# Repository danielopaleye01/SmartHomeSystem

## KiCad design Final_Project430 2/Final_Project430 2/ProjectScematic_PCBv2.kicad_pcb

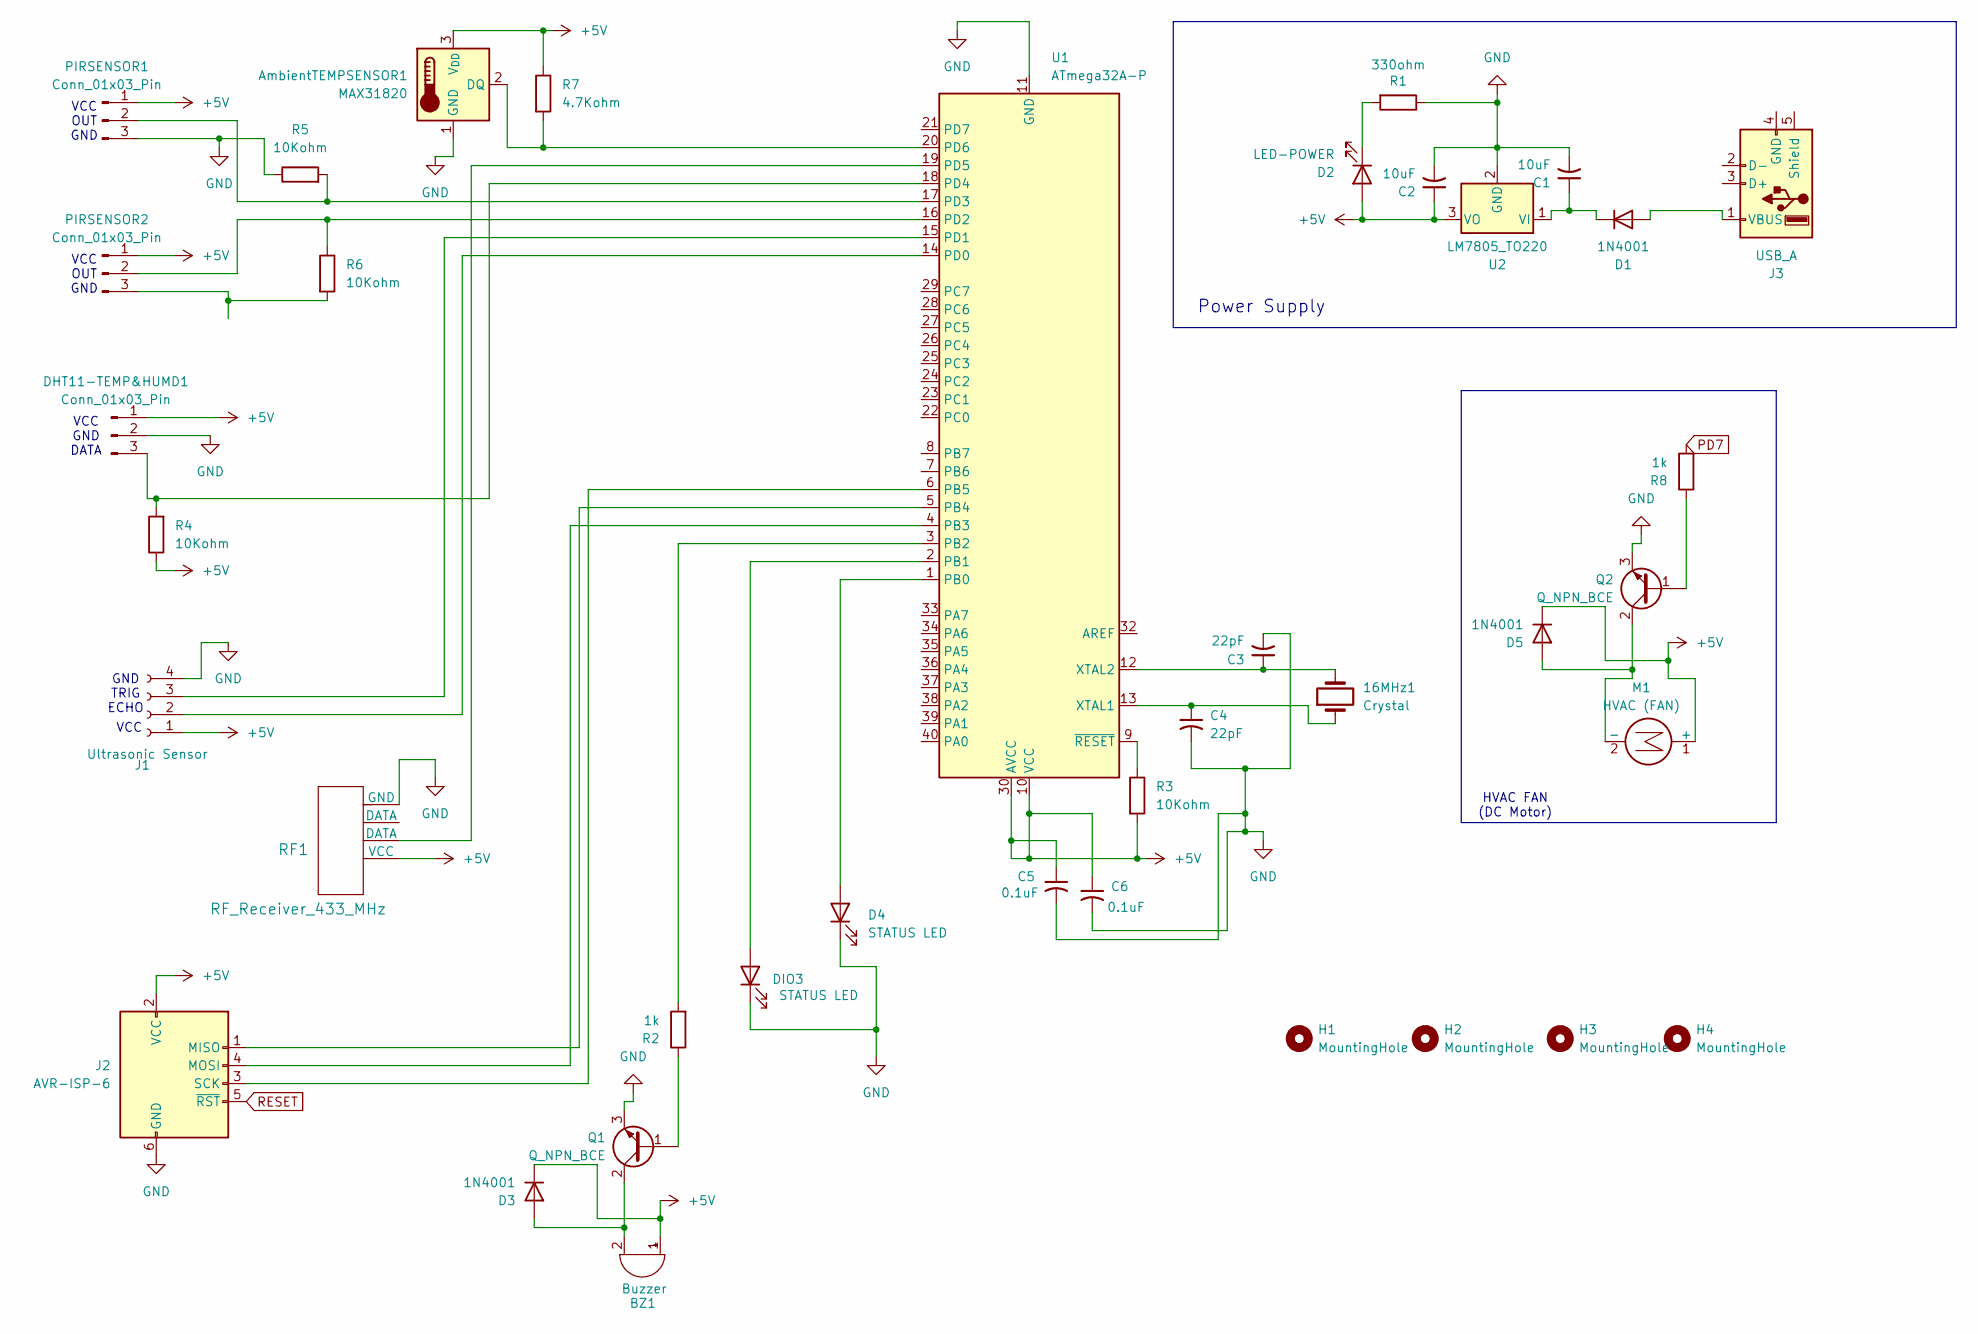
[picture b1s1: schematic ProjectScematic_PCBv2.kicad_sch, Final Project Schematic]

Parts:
16MHz1: Crystal; Crystal_HC49-U_Vertical
AmbientTEMPSENSOR1: MAX31820; TO-92_Inline
BZ1: Buzzer; Buzzer_12x9.5RM7.6
C1, C2: 10uF; C_Elec_5x5.4
C3, C4: 22pF; C_Elec_5x5.4
C5, C6: 0.1uF; C_Elec_5x5.4
D1, D3, D5: 1N4001; D_DO-41_SOD81_P10.16mm_Horizontal
D2: LED-POWER; LED_PLCC-2_3x2mm_AK
D4: STATUS LED; LED_1W_3W_R8
DHT11-TEMP&HUMD1: Conn_01x03_Pin; PinSocket_1x03_P2.54mm_Vertical
DIO3: STATUS LED; LED-L1T2_LUMILEDS
H1, H2, H3, H4: MountingHole; MountingHole_2.1mm
J1: Ultrasonic Sensor; AMS_OLGA12
J2: AVR-ISP-6; PinHeader_2x03_P2.54mm_Vertical
J3: USB_A; USB_A_CNCTech_1001-011-01101_Horizontal
M1: HVAC (FAN); FanPinHeader_1x03_P2.54mm_Vertical
PIRSENSOR1, PIRSENSOR2: Conn_01x03_Pin; FanPinHeader_1x03_P2.54mm_Vertical
Q1, Q2: Q_NPN_BCE; GaN_Systems_GaNPX-3_5x6.6mm_Drain2.93x0.6mm
R1: 330ohm; R_0201_0603Metric_Pad0.64x0.40mm_HandSolder
R2, R8: 1k; R_0201_0603Metric_Pad0.64x0.40mm_HandSolder
R3, R4, R5, R6: 10Kohm; R_0201_0603Metric_Pad0.64x0.40mm_HandSolder
R7: 4.7Kohm; R_0201_0603Metric_Pad0.64x0.40mm_HandSolder
RF1: RF_Receiver_433_MHz; Skyworks_SKY65404-31
U1: ATmega32A-P; DIP-40_W15.24mm
U2: LM7805_TO220; TO-220-3_Vertical

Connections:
+5V: AmbientTEMPSENSOR1.3 (V_{DD}), BZ1.1 (+), C2.1, C5.1, C6.1, D2.2 (A), D3.1 (K), D5.1 (K), DHT11-TEMP&HUMD1.1, J1.1, J2.2 (VCC), M1.1 (+), PIRSENSOR1.1, PIRSENSOR2.1, R3.2, R4.1, R7.1, RF1.1 (VCC), U1.10 (VCC), U1.30 (AVCC), U2.3 (VO)
GND: AmbientTEMPSENSOR1.1 (GND), C1.2, C2.2, C3.2, C4.2, C5.2, C6.2, D4.1 (K), DHT11-TEMP&HUMD1.2, DIO3.1 (K), J1.4, J2.6 (GND), PIRSENSOR1.3, Q1.3 (E), Q2.3 (E), R1.1, R5.1, RF1.4 (GND), U1.11 (GND), U1.31 (GND), U2.2 (GND)
unnamed: AmbientTEMPSENSOR1.2 (DQ), R7.2, U1.20 (PD6)
unnamed: BZ1.2 (-), D3.2 (A), Q1.2 (C)
unnamed: D1.2 (A), J3.1 (VBUS)
unnamed: C1.1, D1.1 (K), U2.1 (VI)
unnamed: D2.1 (K), R1.2
unnamed: D4.2 (A), U1.1 (PB0)
unnamed: D5.2 (A), M1.2 (-), Q2.2 (C)
unnamed: DHT11-TEMP&HUMD1.3, R4.2, U1.18 (PD4)
unnamed: DIO3.2 (A), U1.2 (PB1)
unnamed: J1.2, U1.14 (PD0)
unnamed: J1.3, U1.15 (PD1)
unnamed: J2.1 (MISO), U1.5 (PB4)
unnamed: J2.4 (MOSI), U1.4 (PB3)
unnamed: J2.3 (SCK), U1.6 (PB5)
unnamed: PIRSENSOR1.2, R5.2, U1.17 (PD3)
unnamed: PIRSENSOR2.2, R6.1, U1.16 (PD2)
unnamed: PIRSENSOR2.3, R6.2
unnamed: Q1.1 (B), R2.1
unnamed: Q2.1 (B), R8.1
unnamed: R2.2, U1.3 (PB2)
unnamed: RF1.2 (DATA), U1.19 (PD5)
unnamed: 16MHz1.1, C4.1, U1.13 (XTAL1)
unnamed: 16MHz1.2, C3.1, U1.12 (XTAL2)
unnamed: R3.1, U1.9 (~RESET)
PD7: R8.2
RESET: J2.5 (~RST)

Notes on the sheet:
VCC GND DATA
VCC
VCC OUT GND
HVAC FAN (DC Motor)
Power Supply
GND TRIG ECHO

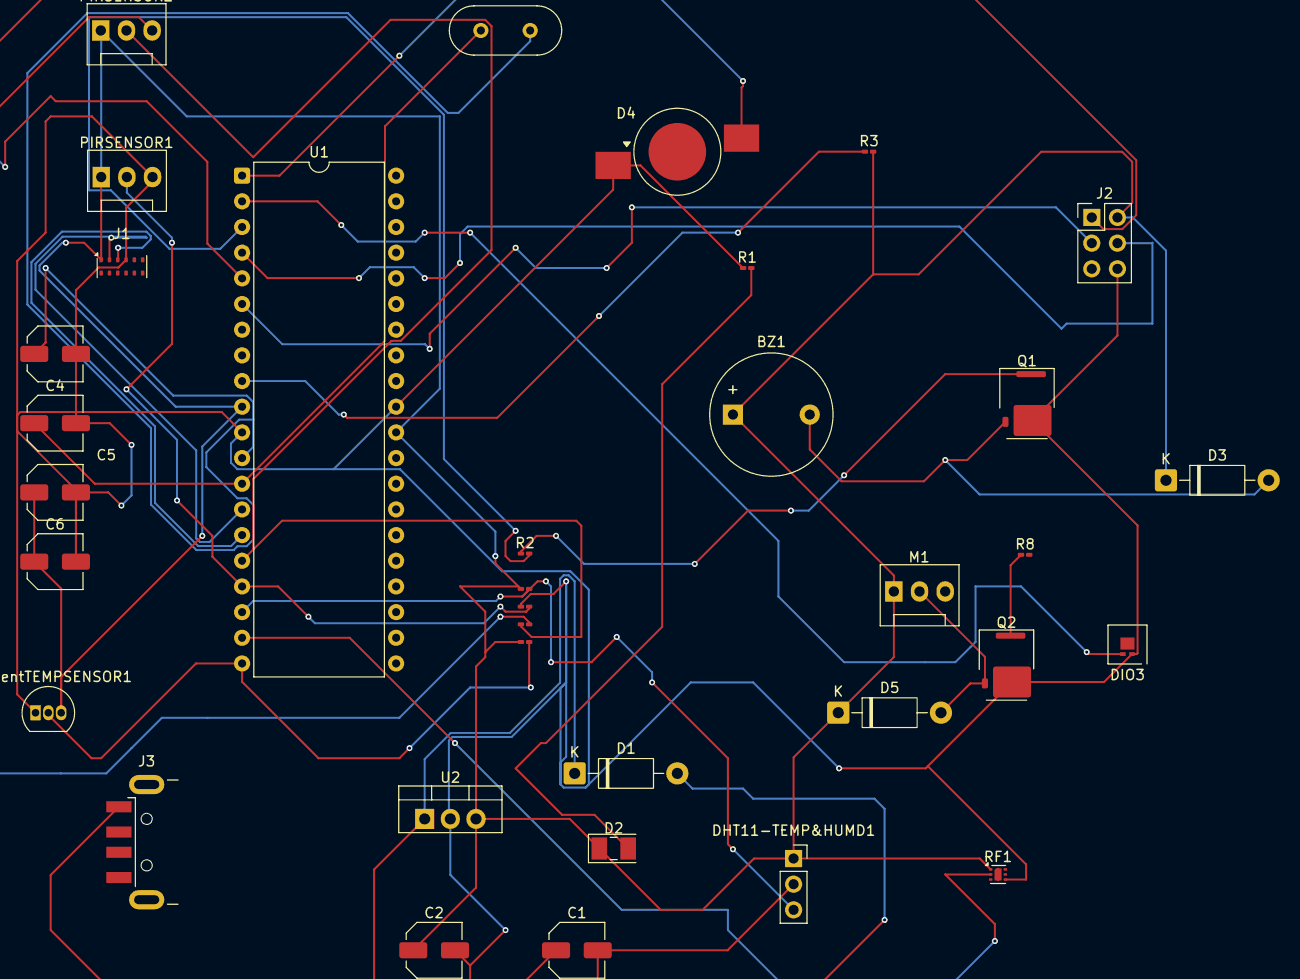
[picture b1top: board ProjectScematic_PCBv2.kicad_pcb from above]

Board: 2 copper layers, 39 parts (0 on the bottom side), 26 nets.

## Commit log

2025-01-28 Create Logbook
2025-01-28 Create Priorities and Dependencies
2025-02-04 Add files via upload
    3 Prototype types
2025-03-11 Updated Logbook
    Included test and development log from past 2 days.
2025-03-11 Update Logbook
2025-03-11 Update Logbook
    Appended final test log.
2025-05-14 Rename Logbook (1) (1).txt to Logbook .txt
2025-05-15 Code for Smart Home system
2025-05-15 KiCad Zip Folder
2025-05-15 Gerber Files Zip Folder
2025-05-15 Drill File
2025-05-15 Gerber and Drill Files
    Compressed folder containing the Gerber and Drill files
2025-05-15 Delete pcb layout-job.gbrjob
    Reuploaded Gerber file folder with Drill files (including this one). Deleting this one here to avoid redundancy.
2025-05-15 Delete Final_Project430 2.zip
    A newer folder was uploaded.
2025-05-15 Delete Gerber_and_Drill_Files.zip
    These were outdated.
